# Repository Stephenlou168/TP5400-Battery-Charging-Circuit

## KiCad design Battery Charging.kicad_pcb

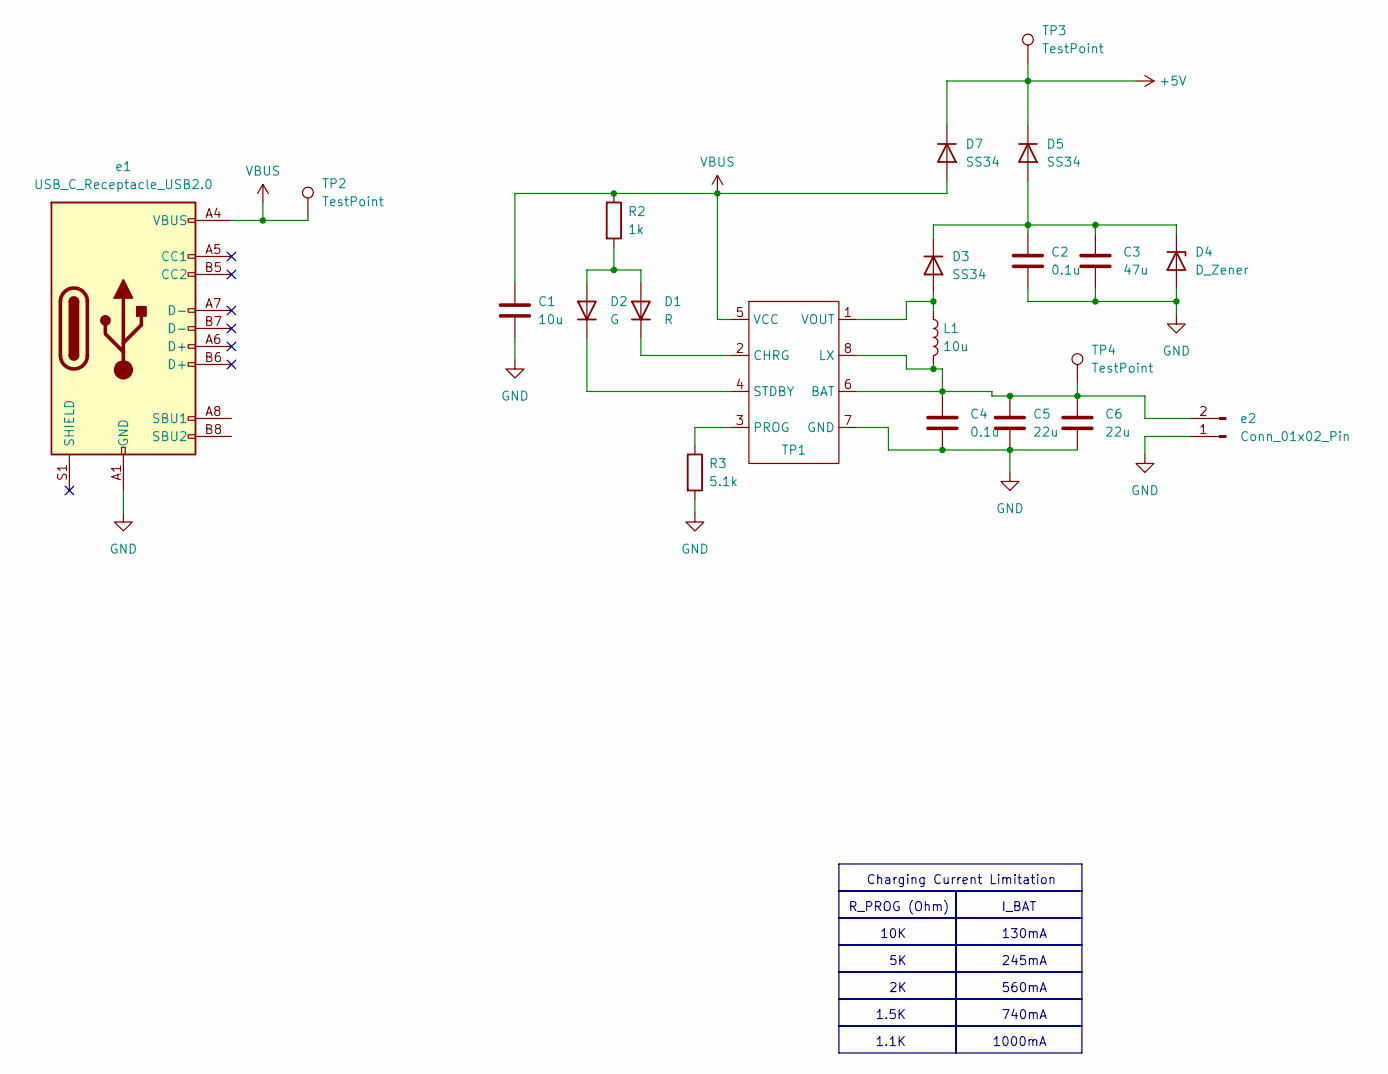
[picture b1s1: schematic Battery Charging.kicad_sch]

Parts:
C1: 10u; C_0805_2012Metric
C2, C4: 0.1u; C_0805_2012Metric
C3: 47u; C_0805_2012Metric
C5, C6: 22u; C_0805_2012Metric
D1: R; LED_0805_2012Metric
D2: G; LED_0805_2012Metric
D3, D5, D7: SS34; D_SMA
D4: D_Zener; D_MiniMELF
L1: 10u; L_Sunlord_SWPA5040S
R2: 1k; R_0805_2012Metric
R3: 5.1k; C_0805_2012Metric
TP1: HTSOP-8-1EP_3.9x4.9mm_P1.27mm_EP2.4x3.2mm_ThermalVias
TP2, TP3, TP4: TestPoint; TestPoint_Pad_D2.0mm
e1: USB_C_Receptacle_USB2.0; USB_C_Receptacle_HRO_TYPE-C-31-M-12
e2: Conn_01x02_Pin; JST_PH_S2B-PH-K_1x02_P2.00mm_Horizontal

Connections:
+5V: D5.1 (K), D7.1 (K), TP3.1
GND: C1.2, C2.2, C3.2, C4.2, C5.2, C6.2, D4.2 (A), R3.2, TP1.7 (GND), e1.A1 (GND), e1.A12 (GND), e1.B1 (GND), e1.B12 (GND), e2.1; also elsewhere on the board
unnamed: D1.2 (A), D2.2 (A), R2.2
unnamed: D1.1 (K), TP1.2 (CHRG)
unnamed: D2.1 (K), TP1.4 (STDBY)
unnamed: D3.2 (A), L1.1, TP1.1 (VOUT)
unnamed: C2.1, C3.1, D3.1 (K), D4.1 (K), D5.2 (A)
unnamed 7: C4.1, C5.1, C6.1, L1.2, TP1.6 (BAT), TP1.8 (LX), TP4.1, e2.2; also elsewhere on the board
unnamed: R3.1, TP1.3 (PROG)
VBUS: C1.1, D7.2 (A), R2.1, TP1.5 (VCC), TP2.1, e1.A4 (VBUS), e1.A9 (VBUS), e1.B4 (VBUS), e1.B9 (VBUS); also elsewhere on the board

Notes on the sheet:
130mA
1.5K
I_BAT
245mA
R_PROG (Ohm)
560mA
Charging Current Limitation
1000mA
740mA
10K
1.1K

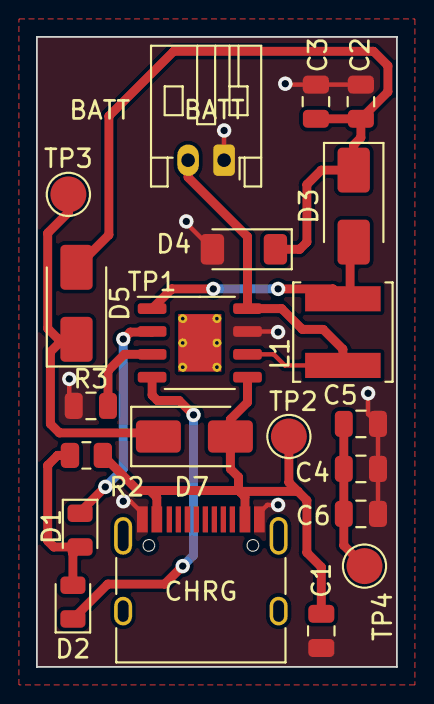
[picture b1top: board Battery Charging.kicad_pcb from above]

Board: 2 copper layers, 20.0 x 35.0 mm, 21 parts (0 on the bottom side), 10 nets.

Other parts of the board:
BATT: Conn_01x02_Pin; JST_PH_S2B-PH-K_1x02_P2.00mm_Horizontal
CHRG: USB_C_Receptacle_USB2.0; USB_C_Receptacle_HRO_TYPE-C-31-M-12

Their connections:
GND: BATT.1, CHRG.A1 (GND), CHRG.A12 (GND), CHRG.B1 (GND), CHRG.B12 (GND); also elsewhere on the board
unnamed 7: BATT.2; also elsewhere on the board
VBUS: CHRG.A4 (VBUS), CHRG.A9 (VBUS), CHRG.B4 (VBUS), CHRG.B9 (VBUS); also elsewhere on the board
